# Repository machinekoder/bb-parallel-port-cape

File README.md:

# BeageBone Parallel Port Cape

This is an open hardware parallel port cape for the BeagleBone.

* [Blog Post about the progress](https://machinekoder.com/working-first-open-source-hardware-parallel-port-cape-beaglebone/)
* [Project at OSH Park](https://oshpark.com/shared_projects/3j2nIZGZ)

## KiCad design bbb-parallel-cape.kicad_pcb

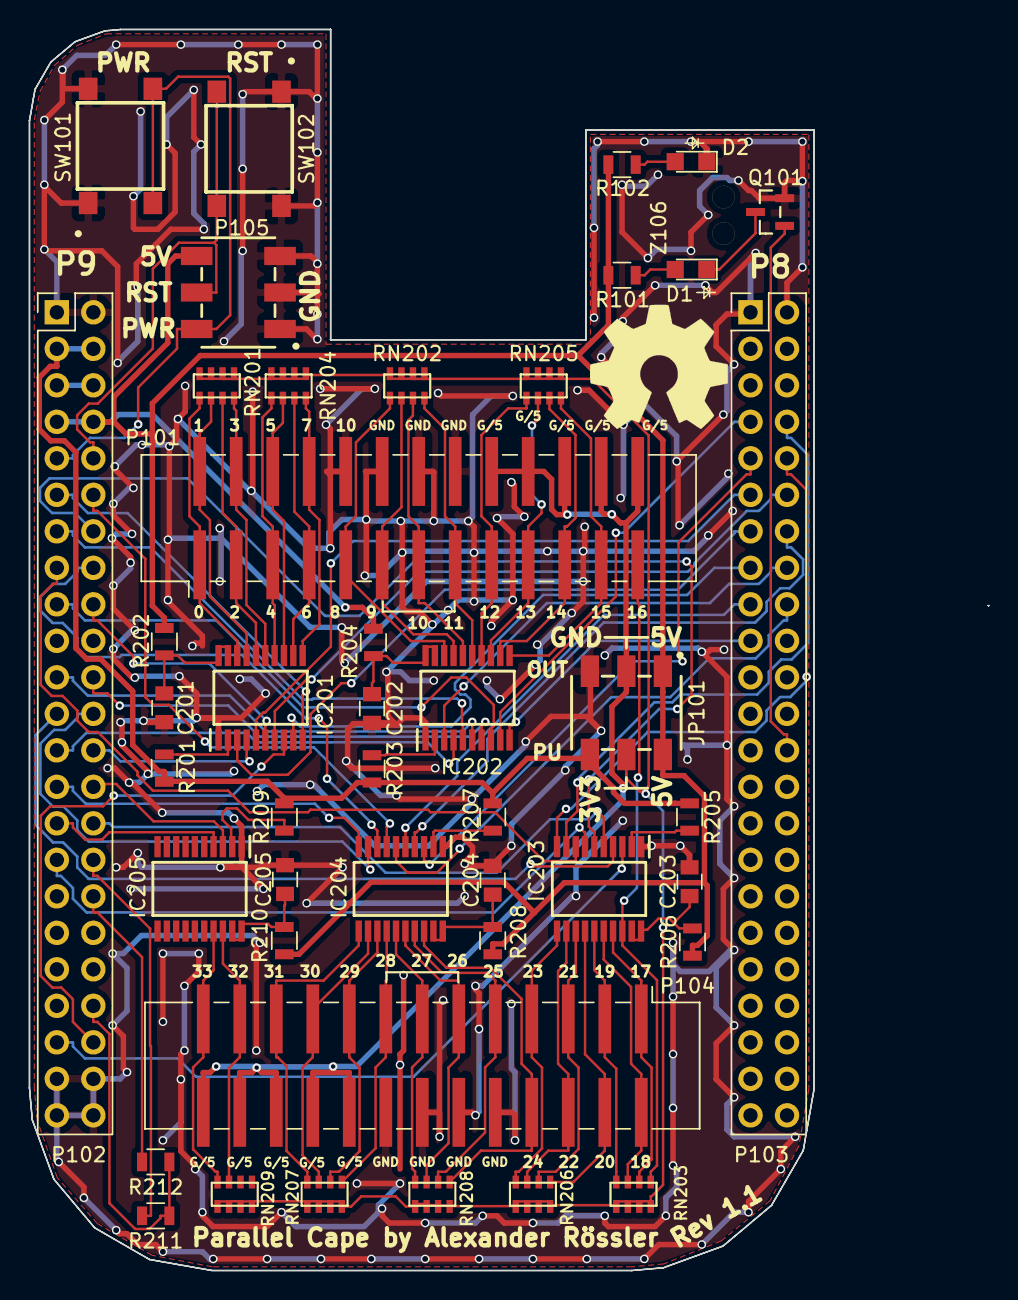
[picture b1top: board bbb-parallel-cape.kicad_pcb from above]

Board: 2 copper layers, 54.6 x 86.4 mm, 45 parts (0 on the bottom side), 93 nets.

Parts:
C201, C202, C203, C204, C205: 0.1u; C_0805
D1: Yellow; LED_0805
D2: Green; LED_0805
IC201, IC202, IC203, IC204, IC205: GTL2003PW; SOP65P640X110-20N
JP101: Jumper_NC_Dual_Double_Header; M20-8760342
P101, P104: IDC26
P102, P103: BeagleBone_Black_Header; Pin_Header_Straight_2x23_Pitch2.54mm
P105: Conn_02x03_Odd_Even; M20-8760342
Q101: 2N7002K; SOT95P240X105-3N
R101, R102: 330; R_0805
R201, R203, R205, R207, R209, R212: 10k; R_0805
R202, R204, R206, R208, R210, R211: 200k; R_0805
RN201, RN202, RN203, RN204, RN205, RN206, RN207, RN208, RN209: 10k; CAT_CAY16
SW101, SW102: SW_Push; PTS645_SMT
Z106: Light_Pipe_2_LED; 515-1114F_2

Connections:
+3V3: JP101.6, P102.3, P102.4, R201.1, R203.1, R205.1, R207.1, R209.1
+5V: P102.5, P102.6
CODING: P102.40, R211.2, R212.1
GNDA_ADC: P102.34, R212.2
GNDD: C201.2, C202.2, C203.2, C204.2, C205.2, D2.1, IC201.1, IC202.1, IC203.1, IC204.1, IC205.1, JP101.5, P101.10, P101.12, P101.14, P101.16, P102.1, P102.2, P102.43, P102.44, P102.45, P102.46, P103.1, P103.2, P104.10, P104.12, P104.14, P104.16, P105.1, P105.3, P105.5, Q101.3, SW101.1, SW102.1
GND_OR_5V: JP101.3, P101.18, P101.20, P101.22, P101.24, P101.26, P104.18, P104.20, P104.22, P104.24, P104.26
IO0: IC201.18, P101.1, RN201.5
IO0_BB: IC201.3, P103.13
IO1: IC201.17, P101.2, RN201.6
IO1_BB: IC201.4, P102.26
IO2: IC201.16, P101.3, RN201.7
IO2_BB: IC201.5, P103.11
IO3: IC201.15, P101.4, RN201.8
IO3_BB: IC201.6, P102.18
IO4: IC201.14, P101.5, RN204.5
IO4_BB: IC201.7, P103.12
IO5: IC201.13, P101.6, RN204.6
IO5_BB: IC201.8, P102.42
IO6: IC201.12, P101.7, RN204.7
IO6_BB: IC201.9, P103.15
IO7: IC201.11, P101.8, RN204.8
IO7_BB: IC201.10, P102.11
IO8: IC202.18, P101.9, RN202.5
IO8_BB: IC202.3, P103.16
IO9: IC202.17, P101.11, RN202.6
IO9_BB: IC202.4, P102.25
IO10: IC202.16, P101.13, RN202.7
IO10_BB: IC202.5, P102.13
IO11: IC202.15, P101.15, RN202.8
IO11_BB: IC202.6, P102.21
IO12: IC202.14, P101.17, RN205.5
IO12_BB: IC202.7, P102.22
IO13: IC202.13, P101.19, RN205.6
IO13_BB: IC202.8, P102.17
IO14: IC202.12, P101.21, RN205.7
IO14_BB: IC202.9, P103.7
IO15: IC202.11, P101.23, RN205.8
IO15_BB: IC202.10, P103.19
IO16: IC203.18, P101.25, RN203.5
IO16_BB: IC203.3, P102.41
IO17: IC203.17, P104.1, RN203.6
IO17_BB: IC203.4, P102.23
IO18: IC203.16, P104.2, RN203.7
IO18_BB: IC203.5, P102.30
IO19: IC203.15, P104.3, RN203.8
IO19_BB: IC203.6, P102.14
IO20: IC203.14, P104.4, RN206.5
IO20_BB: IC203.7, P102.31
IO21: IC203.13, P104.5, RN206.6
IO21_BB: IC203.8, P102.15
IO22: IC203.12, P104.6, RN206.7
IO22_BB: IC203.9, P103.8
IO23: IC203.11, P104.7, RN206.8
IO23_BB: IC203.10, P103.10
IO24: IC204.18, P104.8, RN208.5
IO24_BB: IC204.3, P103.9
IO25: IC204.17, P104.9, RN208.6
IO25_BB: IC204.4, P103.14
IO26: IC204.16, P104.11, RN208.7
IO26_BB: IC204.5, P103.17
IO27: IC204.15, P104.13, RN208.8
IO27_BB: IC204.6, P103.18
IO28: IC204.14, P104.15, RN207.5
IO28_BB: IC204.7, P102.12
IO29: IC204.13, P104.17, RN207.6
IO29_BB: IC204.8, P102.16
IO30: IC204.12, P104.19, RN207.7
IO30_BB: IC204.9, P102.24
IO31: IC204.11, P104.21, RN207.8
IO31_BB: IC204.10, P102.27
IO32: IC205.18, P104.23, RN209.7
IO32_BB: IC205.3, P102.28
IO33: IC205.17, P104.25, RN209.8
IO33_BB: IC205.4, P102.29
unnamed: C201.1, IC201.19, IC201.20, R202.2
unnamed: C202.1, IC202.19, IC202.20, R204.2
unnamed: C203.1, IC203.19, IC203.20, R206.2
unnamed: C204.1, IC204.19, IC204.20, R208.2
unnamed: C205.1, IC205.19, IC205.20, R210.2
unnamed: D1.1, Q101.2
unnamed: D1.2, R101.2
unnamed: D2.2, R102.2
unnamed: IC201.2, R201.2
unnamed: IC202.2, R203.2
unnamed: IC203.2, R205.2
unnamed: IC204.2, R207.2
unnamed: IC205.2, R209.2
PULLUP_REF: JP101.4, RN201.1, RN201.2, RN201.3, RN201.4, RN202.1, RN202.2, RN202.3, RN202.4, RN203.1, RN203.2, RN203.3, RN203.4, RN204.1, RN204.2, RN204.3, RN204.4, RN205.1, RN205.2, RN205.3, RN205.4, RN206.1, RN206.2, RN206.3, RN206.4, RN207.1, RN207.2, RN207.3, RN207.4, RN208.1, RN208.2, RN208.3, RN208.4, RN209.1, RN209.2, RN209.3, RN209.4
PWR_BUT: P102.9, P105.2, SW101.2
STATUS_LED: P103.26, Q101.1
SYS_5V: JP101.1, JP101.2, P102.7, P102.8, P105.6, R101.1, R102.1, R202.1, R204.1, R206.1, R208.1, R210.1
SYS_RESETn: P102.10, P105.4, SW102.2
VDD_ADC: P102.32, R211.1

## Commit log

2018-01-13 before placement
2018-01-13 before edge cut
2018-03-04 revision1 files
2018-03-18 revision 1.1 before via stitching
2018-03-22 completing Rev 1.1
2018-03-22 README: add link
2018-03-22 README: add another link
2018-07-22 updating project
2018-07-22 adding image
